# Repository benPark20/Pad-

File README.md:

# Pad+
This is a numpad and macro pad that I am designing from scratch for personal use

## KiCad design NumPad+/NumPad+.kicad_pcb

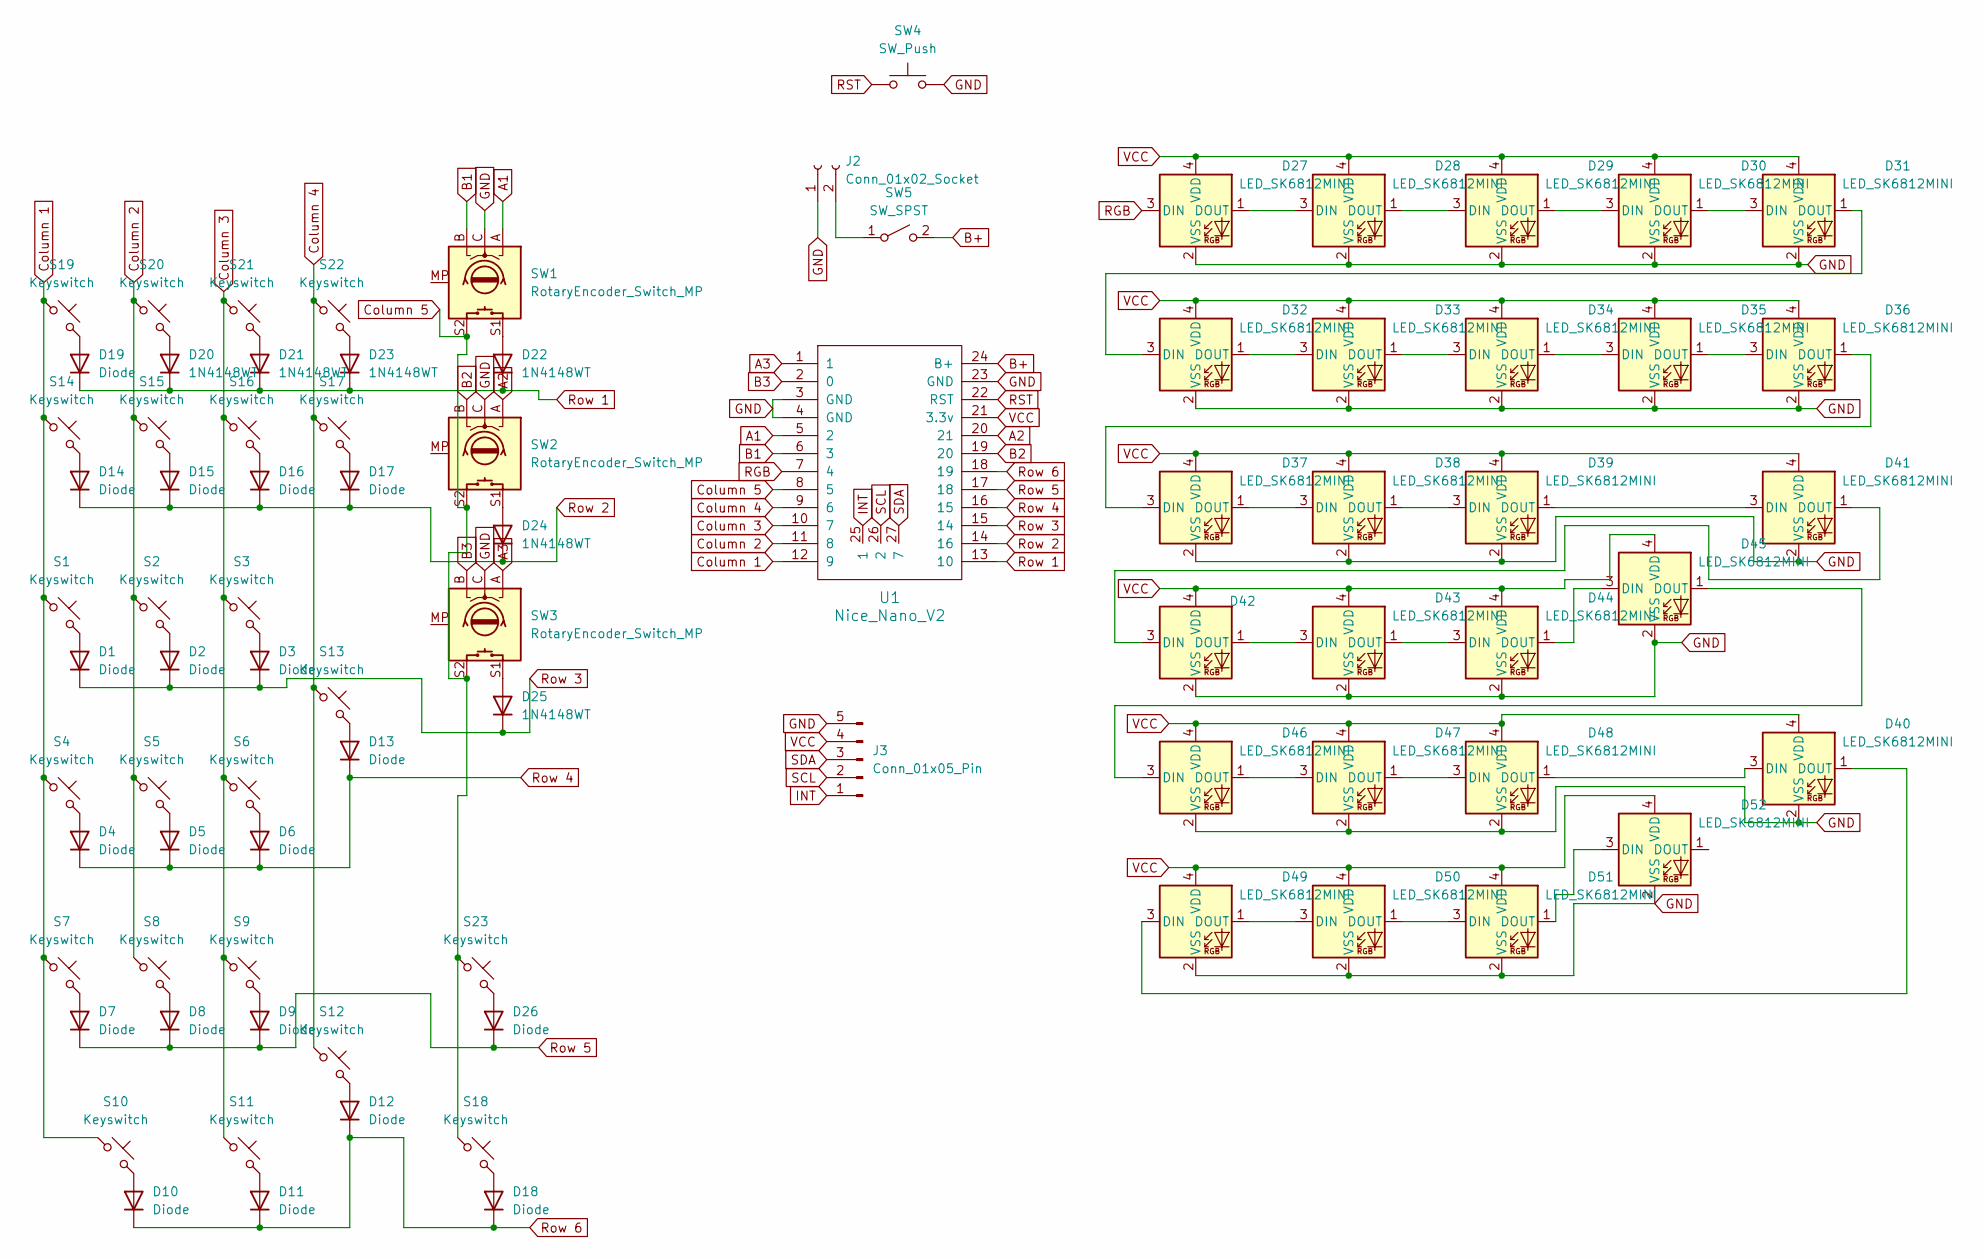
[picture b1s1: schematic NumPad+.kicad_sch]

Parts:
D1, D2, D3, D4, D5, D6, D7, D8, D9, D10, D11, D12, D13, D14, D15, D16, D17, D18, D19, D26: Diode; D_SOD-123
D20, D21, D22, D23, D24, D25: 1N4148WT; D_SOD-123
D27, D28, D29, D30, D31, D32, D33, D34, D35, D36, D37, D38, D39, D40, D41, D42, D43, D44, D45, D46, D47, D48, D49, D50, D51, D52: LED_SK6812MINI; LED_SK6812MINI_PLCC4_3.5x3.5mm_P1.75mm
J2: Conn_01x02_Socket; JST_EH_S2B-EH_1x02_P2.50mm_Horizontal
J3: Conn_01x05_Pin; JST_EH_S5B-EH_1x05_P2.50mm_Horizontal
S1, S2, S3, S4, S5, S6, S7, S8, S9, S10, S11, S12, S13, S14, S15, S16, S17, S18, S19, S20, S21, S22, S23: Keyswitch; SW_Cherry_MX_1.00u_PCB
SW1, SW2, SW3: RotaryEncoder_Switch_MP; RotaryEncoder_Alps_EC11E-Switch_Vertical_H20mm
SW4: SW_Push; Button_MJTP1243
SW5: SW_SPST; SW_SPDT_PCM12
U1: Nice_Nano_V2

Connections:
A1: SW1.A, U1.5 (2)
A2: SW2.A, U1.20 (21)
A3: SW3.A, U1.1
B1: SW1.B, U1.6 (3)
B2: SW2.B, U1.19 (20)
B3: SW3.B, U1.2 (0)
B+: SW5.2 (B), U1.24 (B+)
Column 1: S1.1, S4.1, S7.1, S10.1, S14.1, S19.1, U1.12 (9)
Column 2: S2.1, S5.1, S8.1, S15.1, S20.1, U1.11 (8)
Column 3: S3.1, S6.1, S9.1, S11.1, S16.1, S21.1, U1.10 (7)
Column 4: S12.1, S13.1, S17.1, S22.1, U1.9 (6)
Column 5: S18.1, S23.1, SW1.S2, SW2.S2, SW3.S2, U1.8 (5)
GND: D27.2 (VSS), D28.2 (VSS), D29.2 (VSS), D30.2 (VSS), D31.2 (VSS), D32.2 (VSS), D33.2 (VSS), D34.2 (VSS), D35.2 (VSS), D36.2 (VSS), D37.2 (VSS), D38.2 (VSS), D39.2 (VSS), D40.2 (VSS), D41.2 (VSS), D42.2 (VSS), D43.2 (VSS), D44.2 (VSS), D45.2 (VSS), D46.2 (VSS), D47.2 (VSS), D48.2 (VSS), D49.2 (VSS), D50.2 (VSS), D51.2 (VSS), D52.2 (VSS), J2.1, J3.5, SW1.C, SW2.C, SW3.C, SW4.2, U1.3 (GND), U1.4 (GND), U1.23 (GND)
INT: J3.1, U1.25 (1)
unnamed: D1.2 (A), S1.2
unnamed: D2.2 (A), S2.2
unnamed: D3.2 (A), S3.2
unnamed: D4.2 (A), S4.2
unnamed: D5.2 (A), S5.2
unnamed: D6.2 (A), S6.2
unnamed: D7.2 (A), S7.2
unnamed: D8.2 (A), S8.2
unnamed: D9.2 (A), S9.2
unnamed: D10.2 (A), S10.2
unnamed: D11.2 (A), S11.2
unnamed: D12.2 (A), S12.2
unnamed: D13.2 (A), S13.2
unnamed: D14.2 (A), S14.2
unnamed: D15.2 (A), S15.2
unnamed: D16.2 (A), S16.2
unnamed: D17.2 (A), S17.2
unnamed: D18.2 (A), S18.2
unnamed: D19.2 (A), S19.2
unnamed: D20.2 (A), S20.2
unnamed: D21.2 (A), S21.2
unnamed: D22.2 (A), SW1.S1
unnamed: D23.2 (A), S22.2
unnamed: D24.2 (A), SW2.S1
unnamed: D25.2 (A), SW3.S1
unnamed: D26.2 (A), S23.2
unnamed: D27.1 (DOUT), D28.3 (DIN)
unnamed: D28.1 (DOUT), D29.3 (DIN)
unnamed: D29.1 (DOUT), D30.3 (DIN)
unnamed: D30.1 (DOUT), D31.3 (DIN)
unnamed: D31.1 (DOUT), D32.3 (DIN)
unnamed: D32.1 (DOUT), D33.3 (DIN)
unnamed: D33.1 (DOUT), D34.3 (DIN)
unnamed: D34.1 (DOUT), D35.3 (DIN)
unnamed: D35.1 (DOUT), D36.3 (DIN)
unnamed: D36.1 (DOUT), D37.3 (DIN)
unnamed: D37.1 (DOUT), D38.3 (DIN)
unnamed: D38.1 (DOUT), D39.3 (DIN)
unnamed: D39.1 (DOUT), D41.3 (DIN)
unnamed: D40.3 (DIN), D48.1 (DOUT)
unnamed: D40.1 (DOUT), D49.3 (DIN)
unnamed: D41.1 (DOUT), D42.3 (DIN)
unnamed: D42.1 (DOUT), D43.3 (DIN)
unnamed: D43.1 (DOUT), D44.3 (DIN)
unnamed: D44.1 (DOUT), D45.3 (DIN)
unnamed: D45.1 (DOUT), D46.3 (DIN)
unnamed: D46.1 (DOUT), D47.3 (DIN)
unnamed: D47.1 (DOUT), D48.3 (DIN)
unnamed: D49.1 (DOUT), D50.3 (DIN)
unnamed: D50.1 (DOUT), D51.3 (DIN)
unnamed: D51.1 (DOUT), D52.3 (DIN)
unnamed: J2.2, SW5.1 (A)
RGB: D27.3 (DIN), U1.7 (4)
RST: SW4.1, U1.22 (RST)
Row 1: D19.1 (K), D20.1 (K), D21.1 (K), D22.1 (K), D23.1 (K), U1.13 (10)
Row 2: D14.1 (K), D15.1 (K), D16.1 (K), D17.1 (K), D24.1 (K), U1.14 (16)
Row 3: D1.1 (K), D2.1 (K), D3.1 (K), D25.1 (K), U1.15 (14)
Row 4: D4.1 (K), D5.1 (K), D6.1 (K), D13.1 (K), U1.16 (15)
Row 5: D7.1 (K), D8.1 (K), D9.1 (K), D26.1 (K), U1.17 (18)
Row 6: D10.1 (K), D11.1 (K), D12.1 (K), D18.1 (K), U1.18 (19)
SCL: J3.2, U1.26 (2)
SDA: J3.3, U1.27 (7)
VCC: D27.4 (VDD), D28.4 (VDD), D29.4 (VDD), D30.4 (VDD), D31.4 (VDD), D32.4 (VDD), D33.4 (VDD), D34.4 (VDD), D35.4 (VDD), D36.4 (VDD), D37.4 (VDD), D38.4 (VDD), D39.4 (VDD), D40.4 (VDD), D41.4 (VDD), D42.4 (VDD), D43.4 (VDD), D44.4 (VDD), D45.4 (VDD), D46.4 (VDD), D47.4 (VDD), D48.4 (VDD), D49.4 (VDD), D50.4 (VDD), D51.4 (VDD), D52.4 (VDD), J3.4, U1.21 (3.3v)

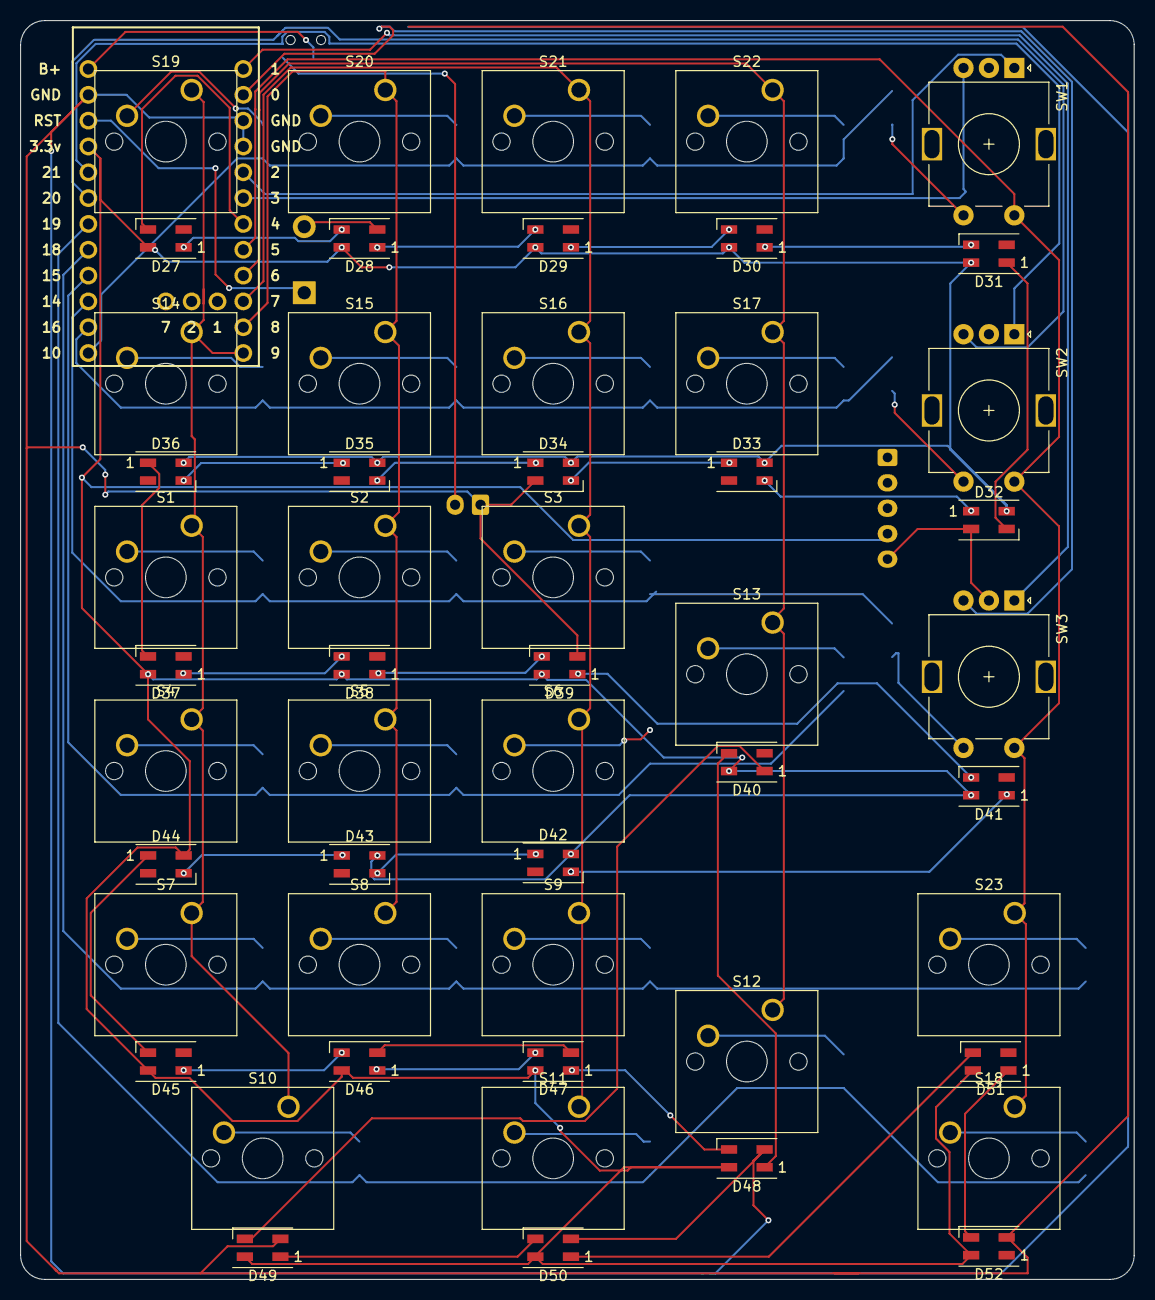
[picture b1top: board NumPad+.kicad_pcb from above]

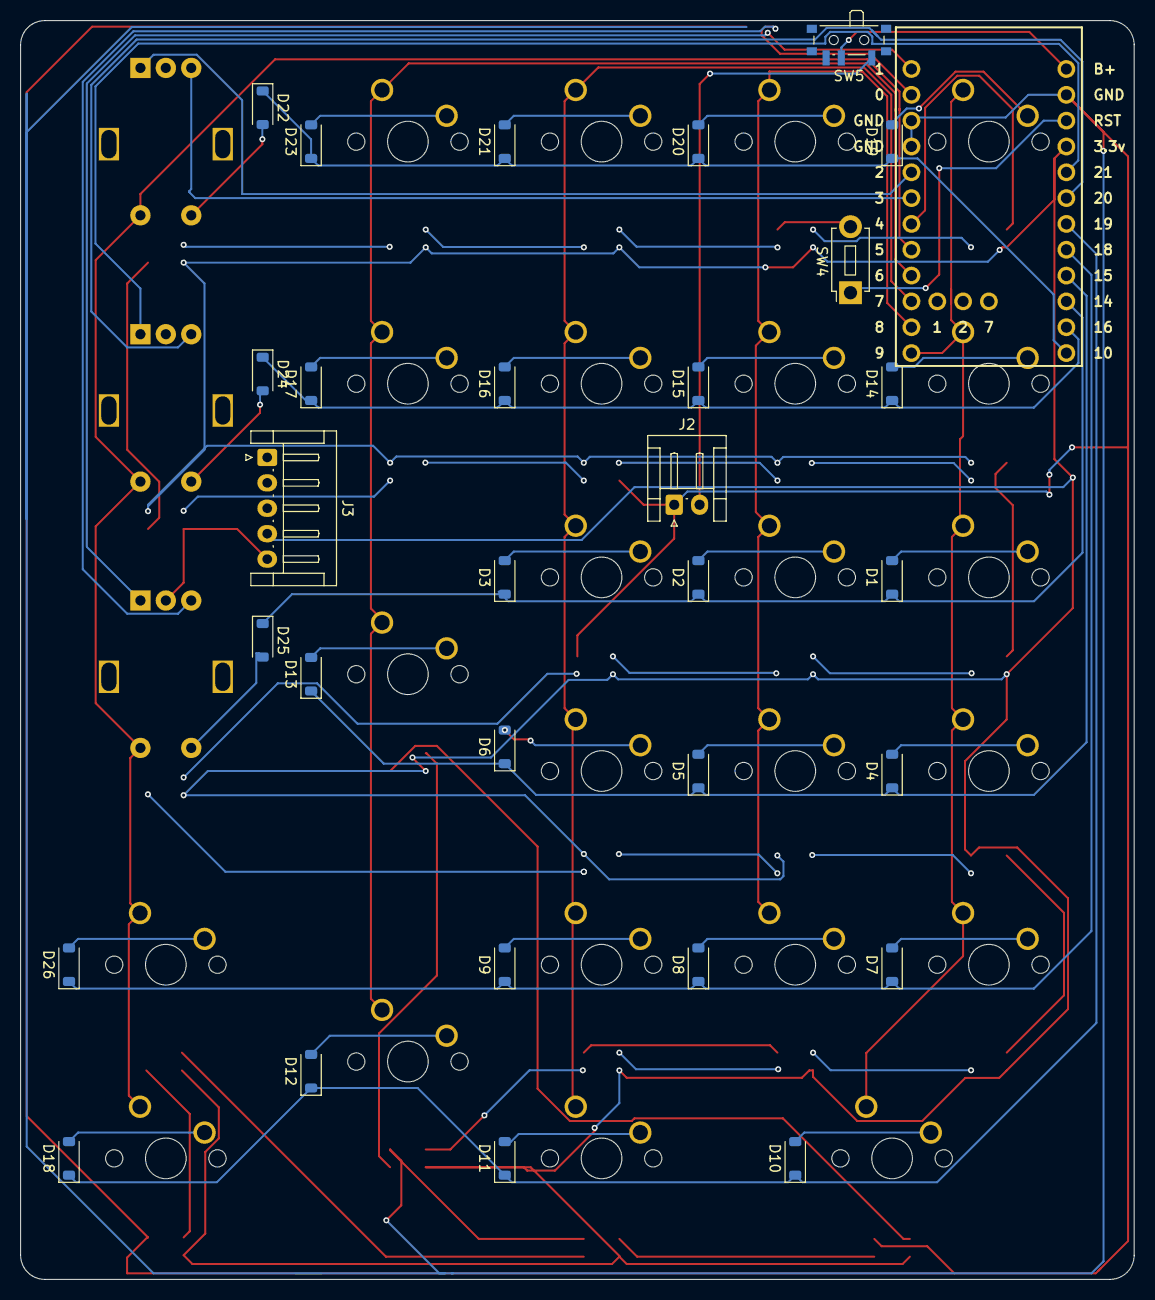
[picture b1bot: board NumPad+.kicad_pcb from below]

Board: 2 copper layers, 109.5 x 123.8 mm, 83 parts (31 on the bottom side), 77 nets.

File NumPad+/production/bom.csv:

Designator,Footprint,Quantity,Value,LCSC Part #
"D1, D10, D11, D12, D13, D14, D15, D16, D17, D18, D19, D2, D26, D3, D4, D5, D6, D7, D8, D9",Diode_SOD-123,20,Diode,
"D20, D21, D22, D23, D24, D25",Diode_SOD-123,6,1N4148WT,
"D27, D28, D29, D30, D31, D32, D33, D34, D35, D36, D37, D38, D39, D40, D41, D42, D43, D44, D45, D46, D47, D48, D49, D50, D51, D52",LED_SK6812MINI_PLCC4_3.5x3.5mm_P1.75mm,26,LED_SK6812MINI,
J1,OLED_128x64,1,OLED_128x64,
J2,JST_EH_S2B-EH_1x02_P2.50mm_Horizontal,1,Conn_01x02_Socket,
"S1, S10, S11, S12, S13, S14, S15, S16, S17, S18, S19, S2, S20, S21, S22, S23, S3, S4, S5, S6, S7, S8, S9",SW_Cherry_MX_1.00u_PCB,23,Keyswitch,
"SW1, SW2, SW3",RotaryEncoder_Alps_EC11E-Switch_Vertical_H20mm,3,RotaryEncoder_Switch_MP,
SW4,Button_MJTP1243,1,SW_Push,
SW5,Switch_MSK12C02,1,SW_SPST,
U1,Nice_Nano_V2,1,Nice_Nano_V2,

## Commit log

2024-07-28 added schematic so far
